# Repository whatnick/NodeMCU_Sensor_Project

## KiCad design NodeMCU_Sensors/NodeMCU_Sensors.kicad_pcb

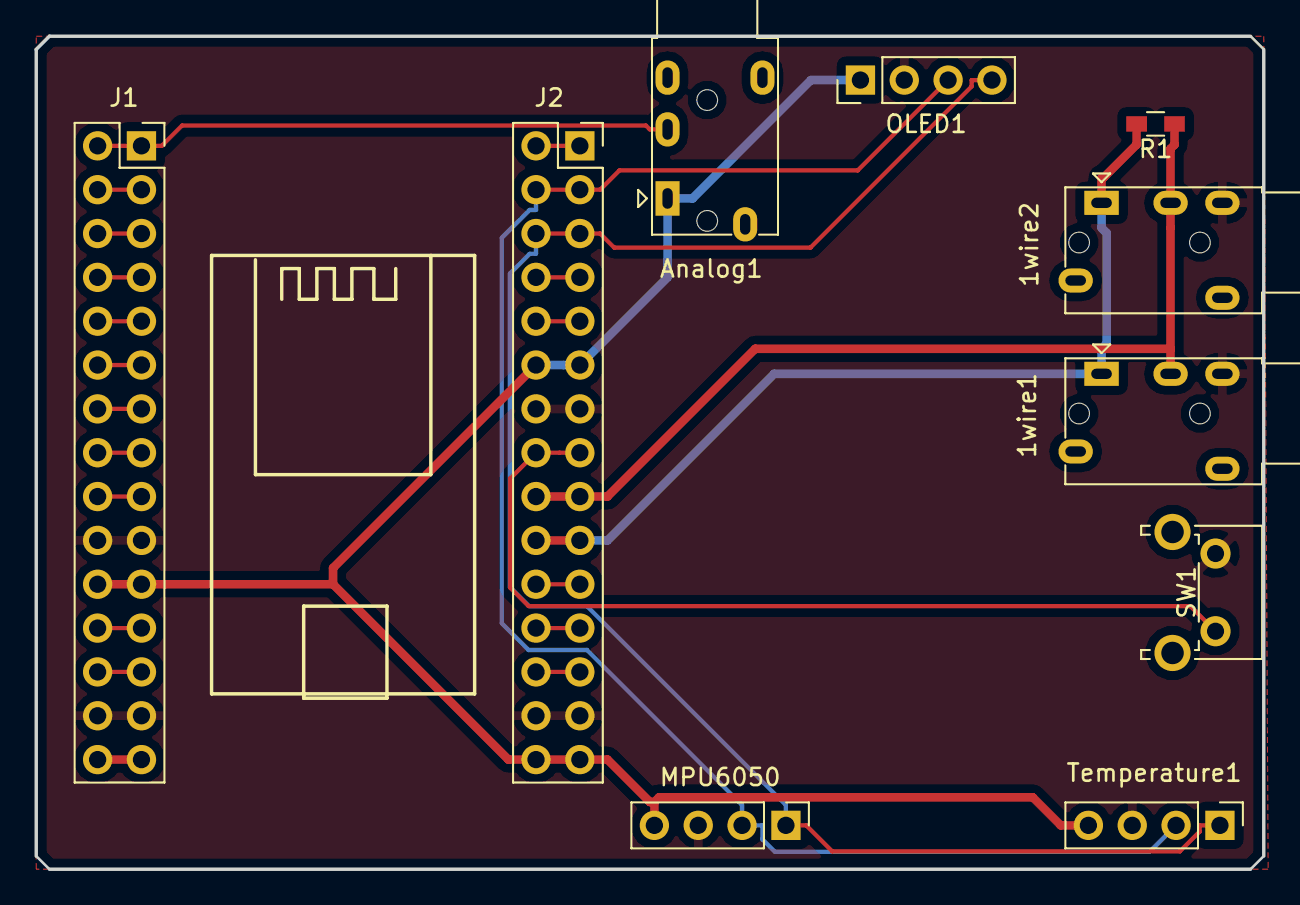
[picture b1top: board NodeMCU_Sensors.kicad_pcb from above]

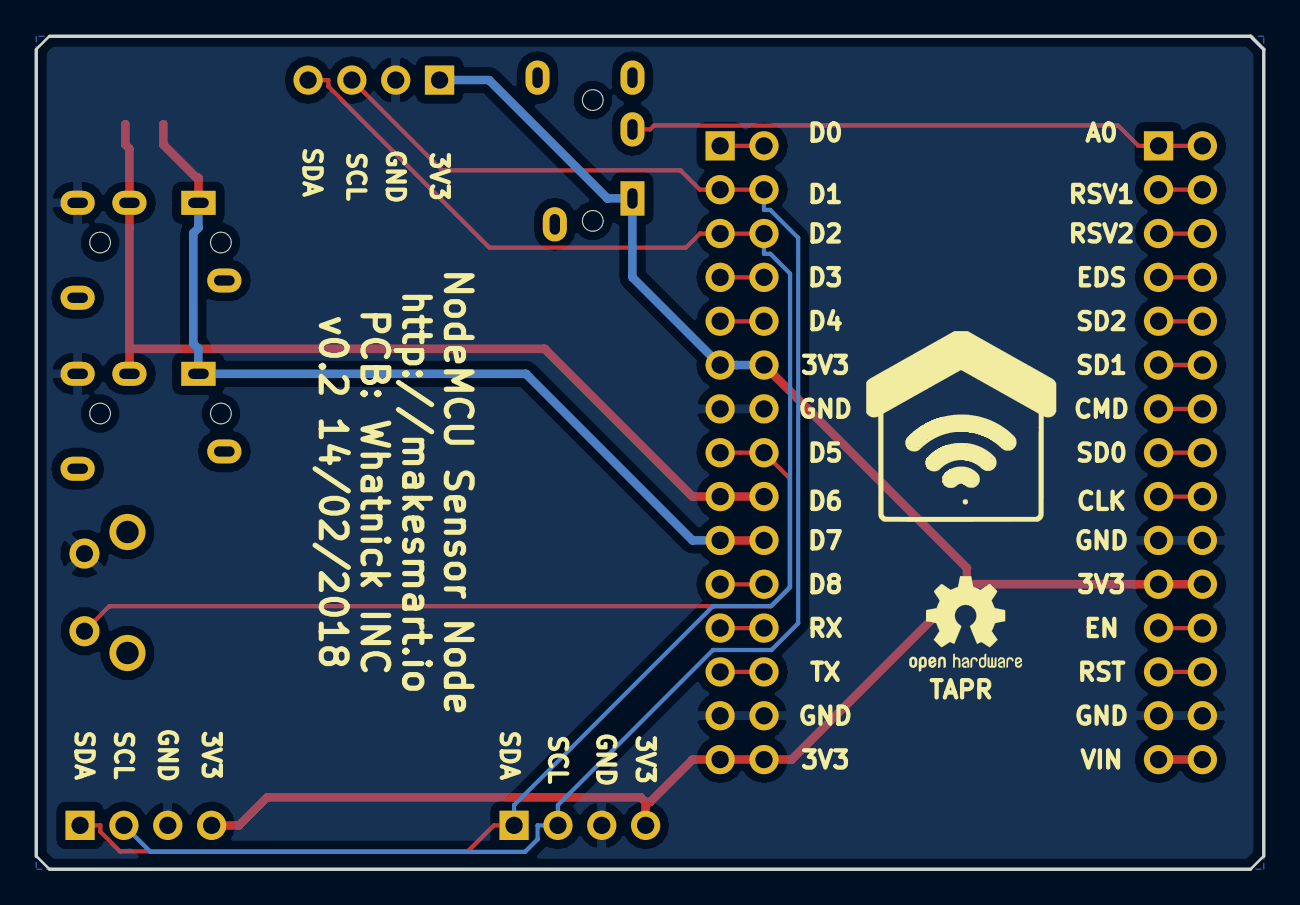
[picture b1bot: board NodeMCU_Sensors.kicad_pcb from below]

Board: 2 copper layers, 71.1 x 48.3 mm, 12 parts (2 on the bottom side), 25 nets.

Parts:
1wire1, 1wire2: Audio-Jack-3_2Switches; Jack_3.5mm_PJ320E_Horizontal
Analog1: Audio-Jack-3_2Switches; Jack_3.5mm_PJ320E_Horizontal
G1: LOGO; makeSmart_logo
G2: Logo_Open_Hardware_Small; OSHW-Logo2_7.3x6mm_SilkScreen
J1, J2: Conn_02x15_Odd_Even; Socket_Strip_Straight_2x15_Pitch2.54mm
MPU6050: Conn_01x04; Socket_Strip_Straight_1x04_Pitch2.54mm
OLED1: Conn_01x04; Socket_Strip_Straight_1x04_Pitch2.54mm
R1: 4.7K; R_0603_HandSoldering
SW1: SW_Push; SW_Tactile_SPST_Angled_PTS645Vx39-2LFS
Temperature1: Conn_01x04; Socket_Strip_Straight_1x04_Pitch2.54mm

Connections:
3V3: Analog1.1, J1.21, J1.22, J2.11, J2.12, J2.29, J2.30, MPU6050.4, OLED1.1, Temperature1.4
A0: Analog1.2, J1.1, J1.2
CLK: J1.17, J1.18
CMD: J1.13, J1.14
D0: J2.1, J2.2
D1: J2.3, J2.4, MPU6050.2, OLED1.3, Temperature1.2
D2: J2.5, J2.6, MPU6050.1, OLED1.4, Temperature1.1
D3: J2.7, J2.8
D4: J2.9, J2.10
D5: J2.15, J2.16, SW1.2
D6: 1wire1.2, 1wire2.2, J2.17, J2.18, R1.1
D7: 1wire1.1, 1wire2.1, J2.19, J2.20, R1.2
D8: J2.21, J2.22
EDS: J1.7, J1.8
EN: J1.23, J1.24
GND: 1wire1.3, 1wire2.3, J1.19, J1.20, J1.27, J1.28, J2.13, J2.14, J2.27, J2.28, MPU6050.3, OLED1.2, SW1.1, Temperature1.3
RST: J1.25, J1.26
RSV1: J1.3, J1.4
RSV2: J1.5, J1.6
RX: J2.23, J2.24
SD0: J1.15, J1.16
SD1: J1.11, J1.12
SD2: J1.9, J1.10
TX: J2.25, J2.26
VIN: J1.29, J1.30

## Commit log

2018-01-25 Add specs documentation
2018-01-25 Added basic parts
2018-01-25 Added placeholder 3D models
2018-01-26 Place parts according to layout plan
2018-01-26 Add possible layout
2018-01-27 Add breakout details
2018-01-27 Wire up i2c sensors
2018-01-27 Route 3.5mm jacks
2018-01-28 Basic autorouted board
2018-01-28 Add version and project name
2018-01-29 Add 3V3 supply to analog pin and re-route
2018-01-30 Adde makesmart logo
2018-02-13 Address #1 for V2 board
2018-02-13 PCB and schema docs
